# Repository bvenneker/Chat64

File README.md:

# CHAT64_C64
Chat64 for Commodore64, Sinclair ZX Spectrum, Atari 800XL, MSX and Amstrad CPC.

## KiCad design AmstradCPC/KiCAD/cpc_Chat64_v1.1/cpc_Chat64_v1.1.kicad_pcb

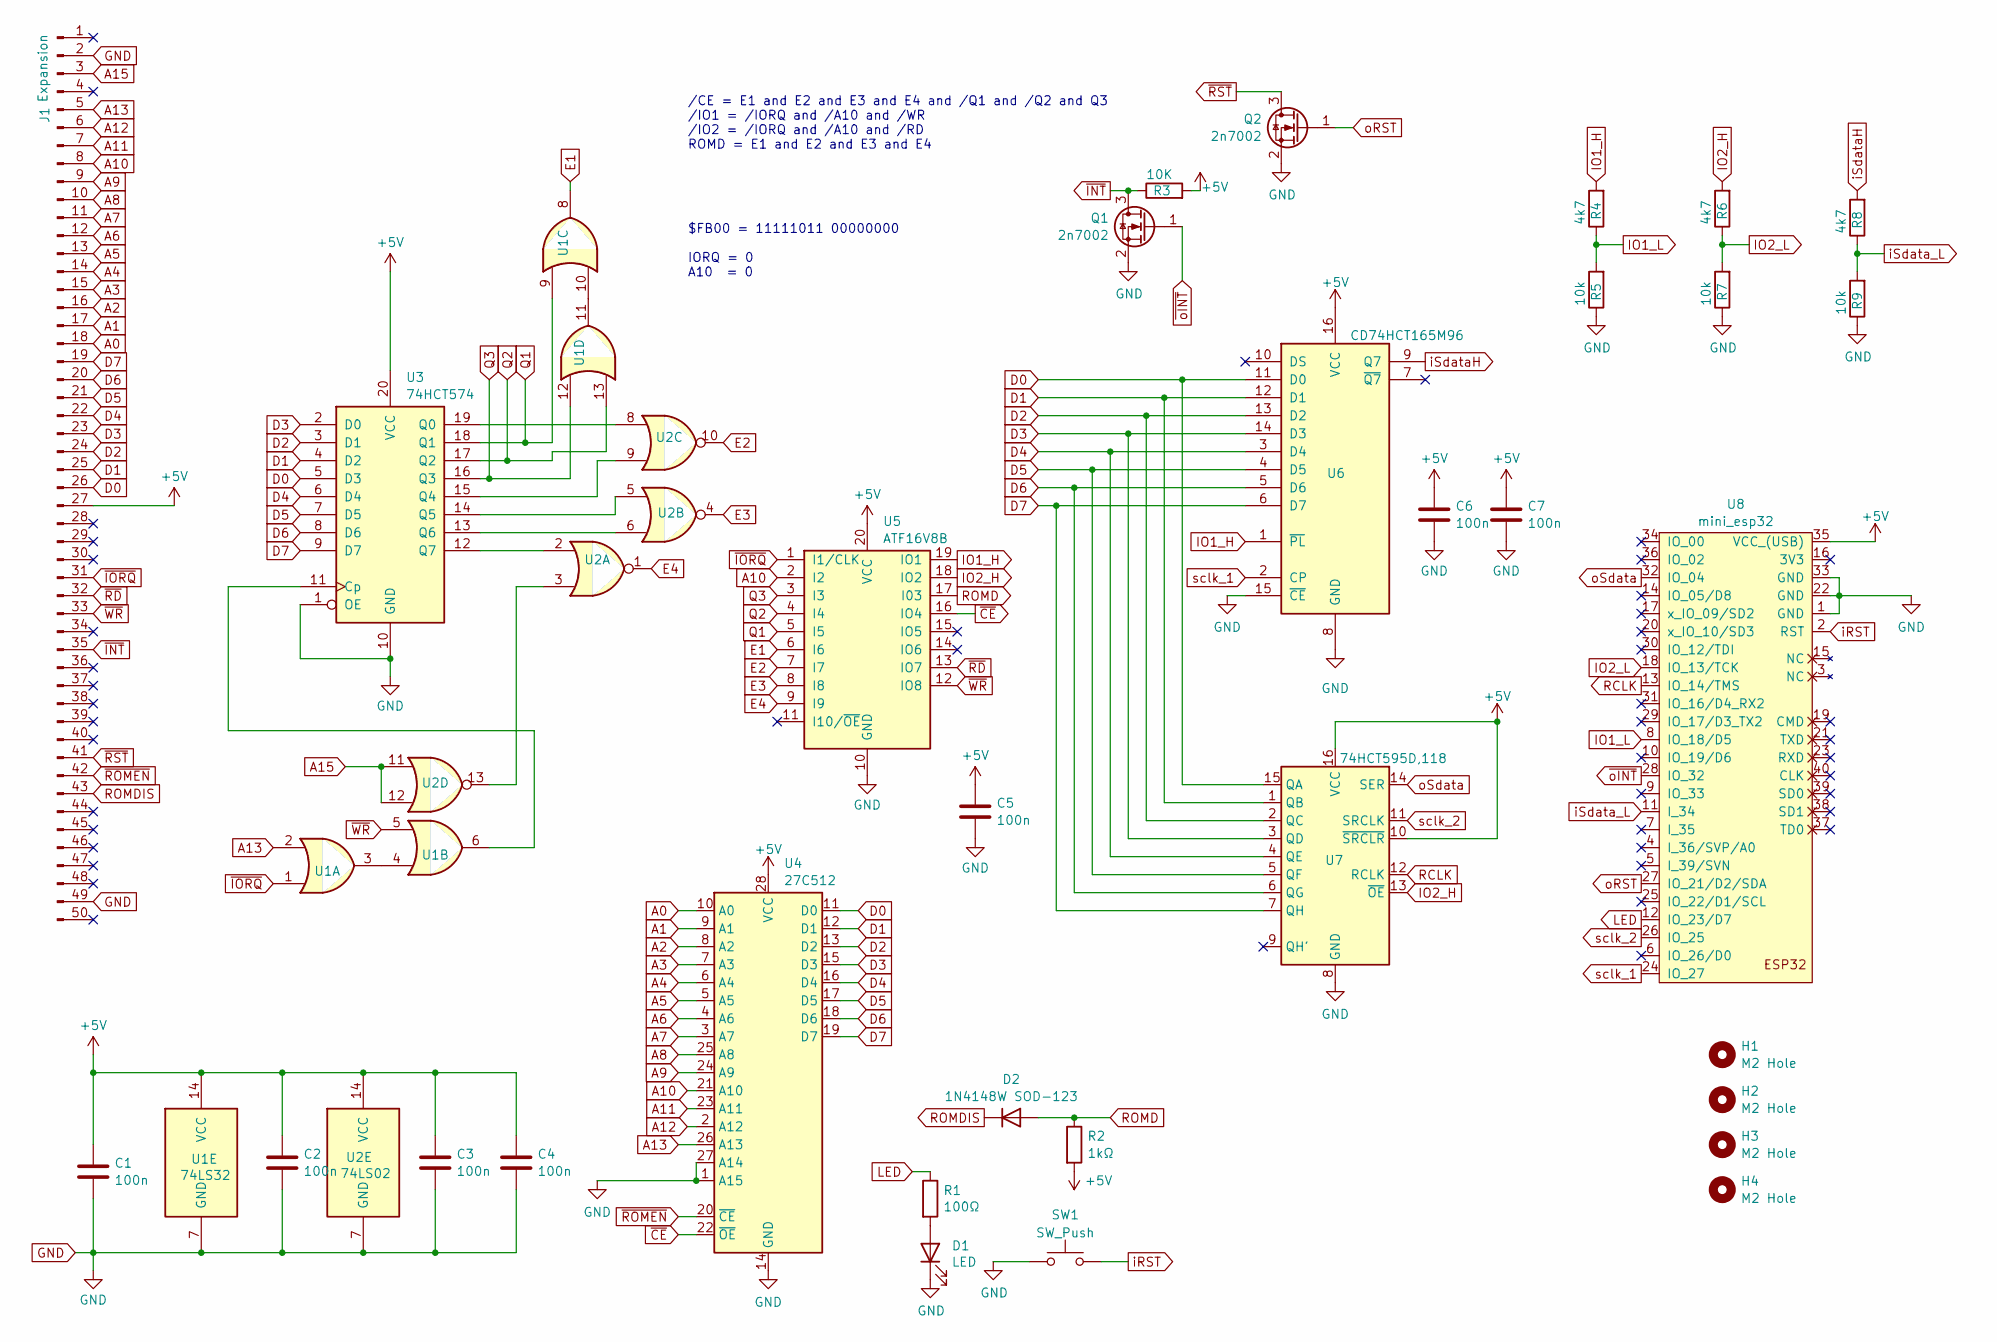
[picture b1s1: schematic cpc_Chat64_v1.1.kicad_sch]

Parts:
C1, C2, C3, C4, C5, C6, C7: 100n; C_0402_1005Metric
D1: LED; LED_0603_1608Metric
D2: 1N4148W SOD-123; D_SOD-123
H1, H2, H3, H4: M2 Hole; MountingHole_2.2mm_M2
J1: Expansion; cpc464_Expansion
Q1, Q2: 2n7002; SOT-23
R1: 100Ω; R_0402_1005Metric
R2: 1kΩ; R_0402_1005Metric
R3: 10K; R_0402_1005Metric
R4, R6, R8: 4k7; R_0402_1005Metric
R5, R7, R9: 10k; R_0402_1005Metric
SW1: SW_Push; SW_PUSH_HALF_6mm
U1: 74LS32; SO-14_3.9x8.65mm_P1.27mm
U2: 74LS02; SO-14_3.9x8.65mm_P1.27mm
U3: 74HCT574; SO-20_5.3x12.6mm_P1.27mm
U4: 27C512; DIP-28_W15.24mm_Socket_LongPads
U5: ATF16V8B; DIP-20_W7.62mm_LongPads
U6: CD74HCT165M96; SOIC-16_3.9x9.9mm_P1.27mm
U7: 74HCT595D,118; SOIC-16_3.9x9.9mm_P1.27mm
U8: mini_esp32; ESP32_mini

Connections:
+5V: C1.1, C2.1, C3.1, C4.1, C5.1, C6.1, C7.1, J1.27, R2.2, R3.2, U1.14 (VCC), U2.14 (VCC), U3.20 (VCC), U4.28 (VCC), U5.20 (VCC), U6.16 (VCC), U7.10 (~SRCLR), U7.16 (VCC), U8.35 (VCC_(USB))
A0: J1.18, U4.10 (A0)
A1: J1.17, U4.9 (A1)
A2: J1.16, U4.8 (A2)
A3: J1.15, U4.7 (A3)
A4: J1.14, U4.6 (A4)
A5: J1.13, U4.5 (A5)
A6: J1.12, U4.4 (A6)
A7: J1.11, U4.3 (A7)
A8: J1.10, U4.25 (A8)
A9: J1.9, U4.24 (A9)
A10: J1.8, U4.21 (A10), U5.2 (I2)
A11: J1.7, U4.23 (A11)
A12: J1.6, U4.2 (A12)
A13: J1.5, U1.2, U4.26 (A13)
A15: J1.3, U2.11, U2.12
D0: J1.26, U3.5 (D3), U4.11 (D0), U6.11 (D0), U7.15 (QA)
D1: J1.25, U3.4 (D2), U4.12 (D1), U6.12 (D1), U7.1 (QB)
D2: J1.24, U3.3 (D1), U4.13 (D2), U6.13 (D2), U7.2 (QC)
D3: J1.23, U3.2 (D0), U4.15 (D3), U6.14 (D3), U7.3 (QD)
D4: J1.22, U3.6 (D4), U4.16 (D4), U6.3 (D4), U7.4 (QE)
D5: J1.21, U3.7 (D5), U4.17 (D5), U6.4 (D5), U7.5 (QF)
D6: J1.20, U3.8 (D6), U4.18 (D6), U6.5 (D6), U7.6 (QG)
D7: J1.19, U3.9 (D7), U4.19 (D7), U6.6 (D7), U7.7 (QH)
E1: U1.8, U5.6 (I6)
E2: U2.10, U5.7 (I7)
E3: U2.4, U5.8 (I8)
E4: U2.1, U5.9 (I9)
GND: C1.2, C2.2, C3.2, C4.2, C5.2, C6.2, C7.2, D1.1 (K), J1.2, J1.49, Q1.2 (S), Q2.2 (S), R5.1, R7.1, R9.1, SW1.1, U1.7 (GND), U2.7 (GND), U3.1 (OE), U3.10 (GND), U4.1 (A15), U4.14 (GND), U4.27 (A14), U5.10 (GND), U6.8 (GND), U6.15 (~CE), U7.8 (GND), U8.1 (GND), U8.22 (GND), U8.33 (GND)
IO1_H: R4.2, U5.19 (IO1), U6.1 (~PL)
IO1_L: R4.1, R5.2, U8.8 (IO_18/D5)
IO2_H: R6.2, U5.18 (IO2), U7.13 (~OE)
IO2_L: R6.1, R7.2, U8.18 (IO_13/TCK)
LED: R1.1, U8.12 (IO_23/D7)
unnamed: D1.2 (A), R1.2
unnamed: U1.3, U1.4
unnamed: U1.10, U1.11
unnamed: U2.3, U2.13
unnamed: U1.6, U3.11 (Cp)
unnamed: U2.8, U3.19 (Q0)
unnamed: U2.9, U3.15 (Q4)
unnamed: U2.5, U3.14 (Q5)
unnamed: U2.6, U3.13 (Q6)
unnamed: U2.2, U3.12 (Q7)
Q1: U1.9, U3.18 (Q1), U5.5 (I5)
Q2: U1.13, U3.17 (Q2), U5.4 (I4)
Q3: U1.12, U3.16 (Q3), U5.3 (I3)
RCLK: U7.12 (RCLK), U8.13 (IO_14/TMS)
ROMD: D2.2 (A), R2.1, U5.17 (I03)
ROMDIS: D2.1 (K), J1.43
iRST: SW1.2, U8.2 (RST)
iSdataH: R8.2, U6.9 (Q7)
iSdata_L: R8.1, R9.2, U8.11 (I_34)
oRST: Q2.1 (G), U8.27 (IO_21/D2/SDA)
oSdata: U7.14 (SER), U8.32 (IO_04)
sclk_1: U6.2 (CP), U8.24 (IO_27)
sclk_2: U7.11 (SRCLK), U8.26 (IO_25)
~CE: U4.22 (~OE), U5.16 (IO4)
~INT: J1.35, Q1.3 (D), R3.1
~IORQ: J1.31, U1.1, U5.1 (I1/CLK)
~RD: J1.32, U5.13 (IO7)
~ROMEN: J1.42, U4.20 (~CE)
~RST: J1.41, Q2.3 (D)
~WR: J1.33, U1.5, U5.12 (IO8)
~oINT: Q1.1 (G), U8.28 (IO_32)

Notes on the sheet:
/CE = E1 and E2 and E3 and E4 and /Q1 and /Q2 and Q3 /IO1 = /IORQ and /A10 and /WR /IO2 = /IORQ and /A10 and /RD ROMD = E1 and E2 and E3 and E4
$FB00 = 11111011 00000000 IORQ = 0 A10 = 0

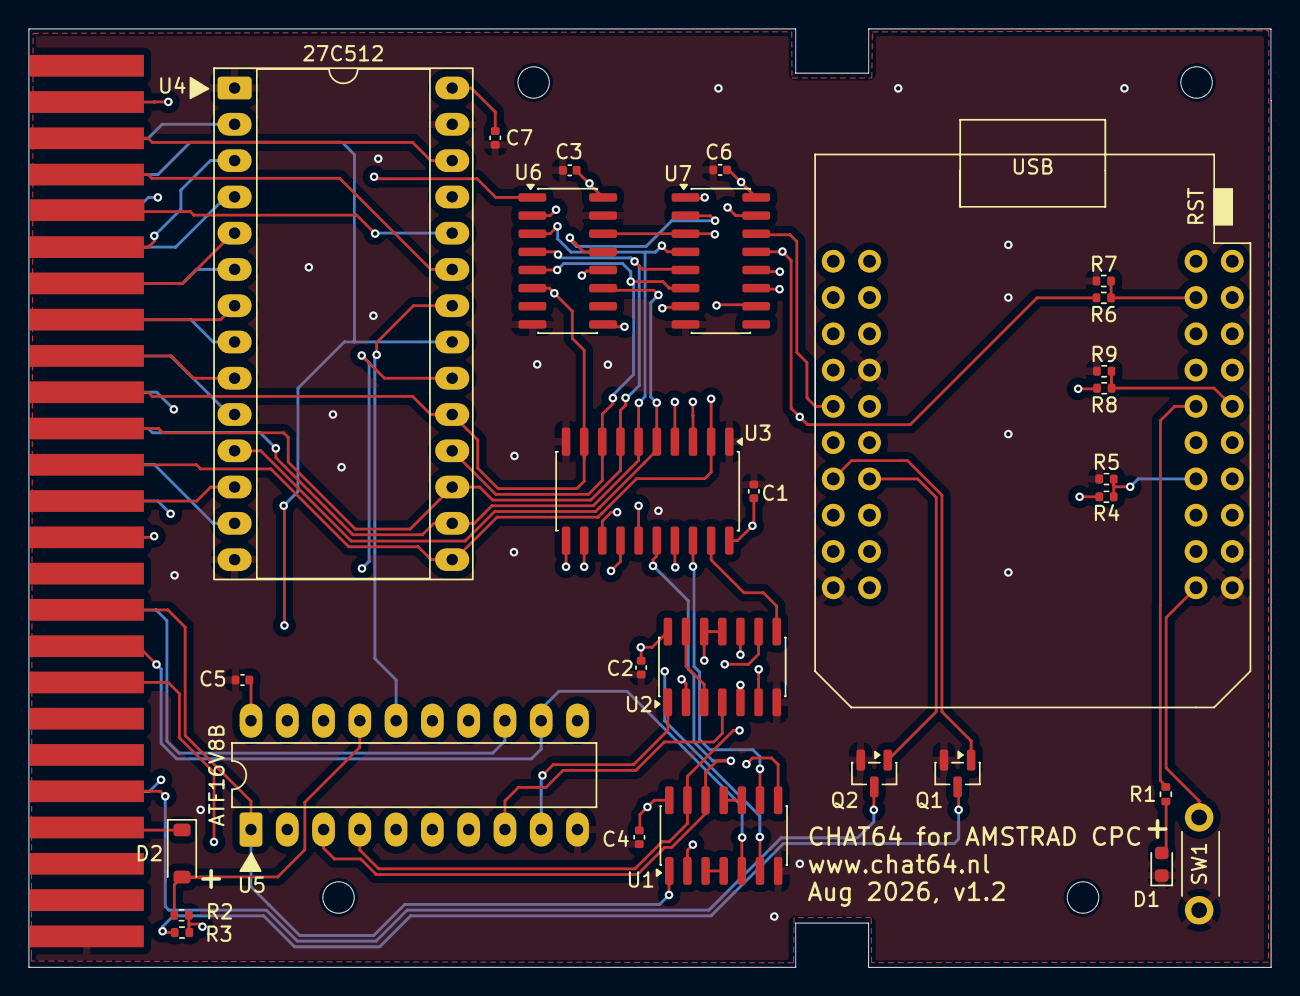
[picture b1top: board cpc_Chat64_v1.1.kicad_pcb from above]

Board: 4 copper layers, 87.0 x 65.7 mm, 34 parts (0 on the bottom side), 65 nets.

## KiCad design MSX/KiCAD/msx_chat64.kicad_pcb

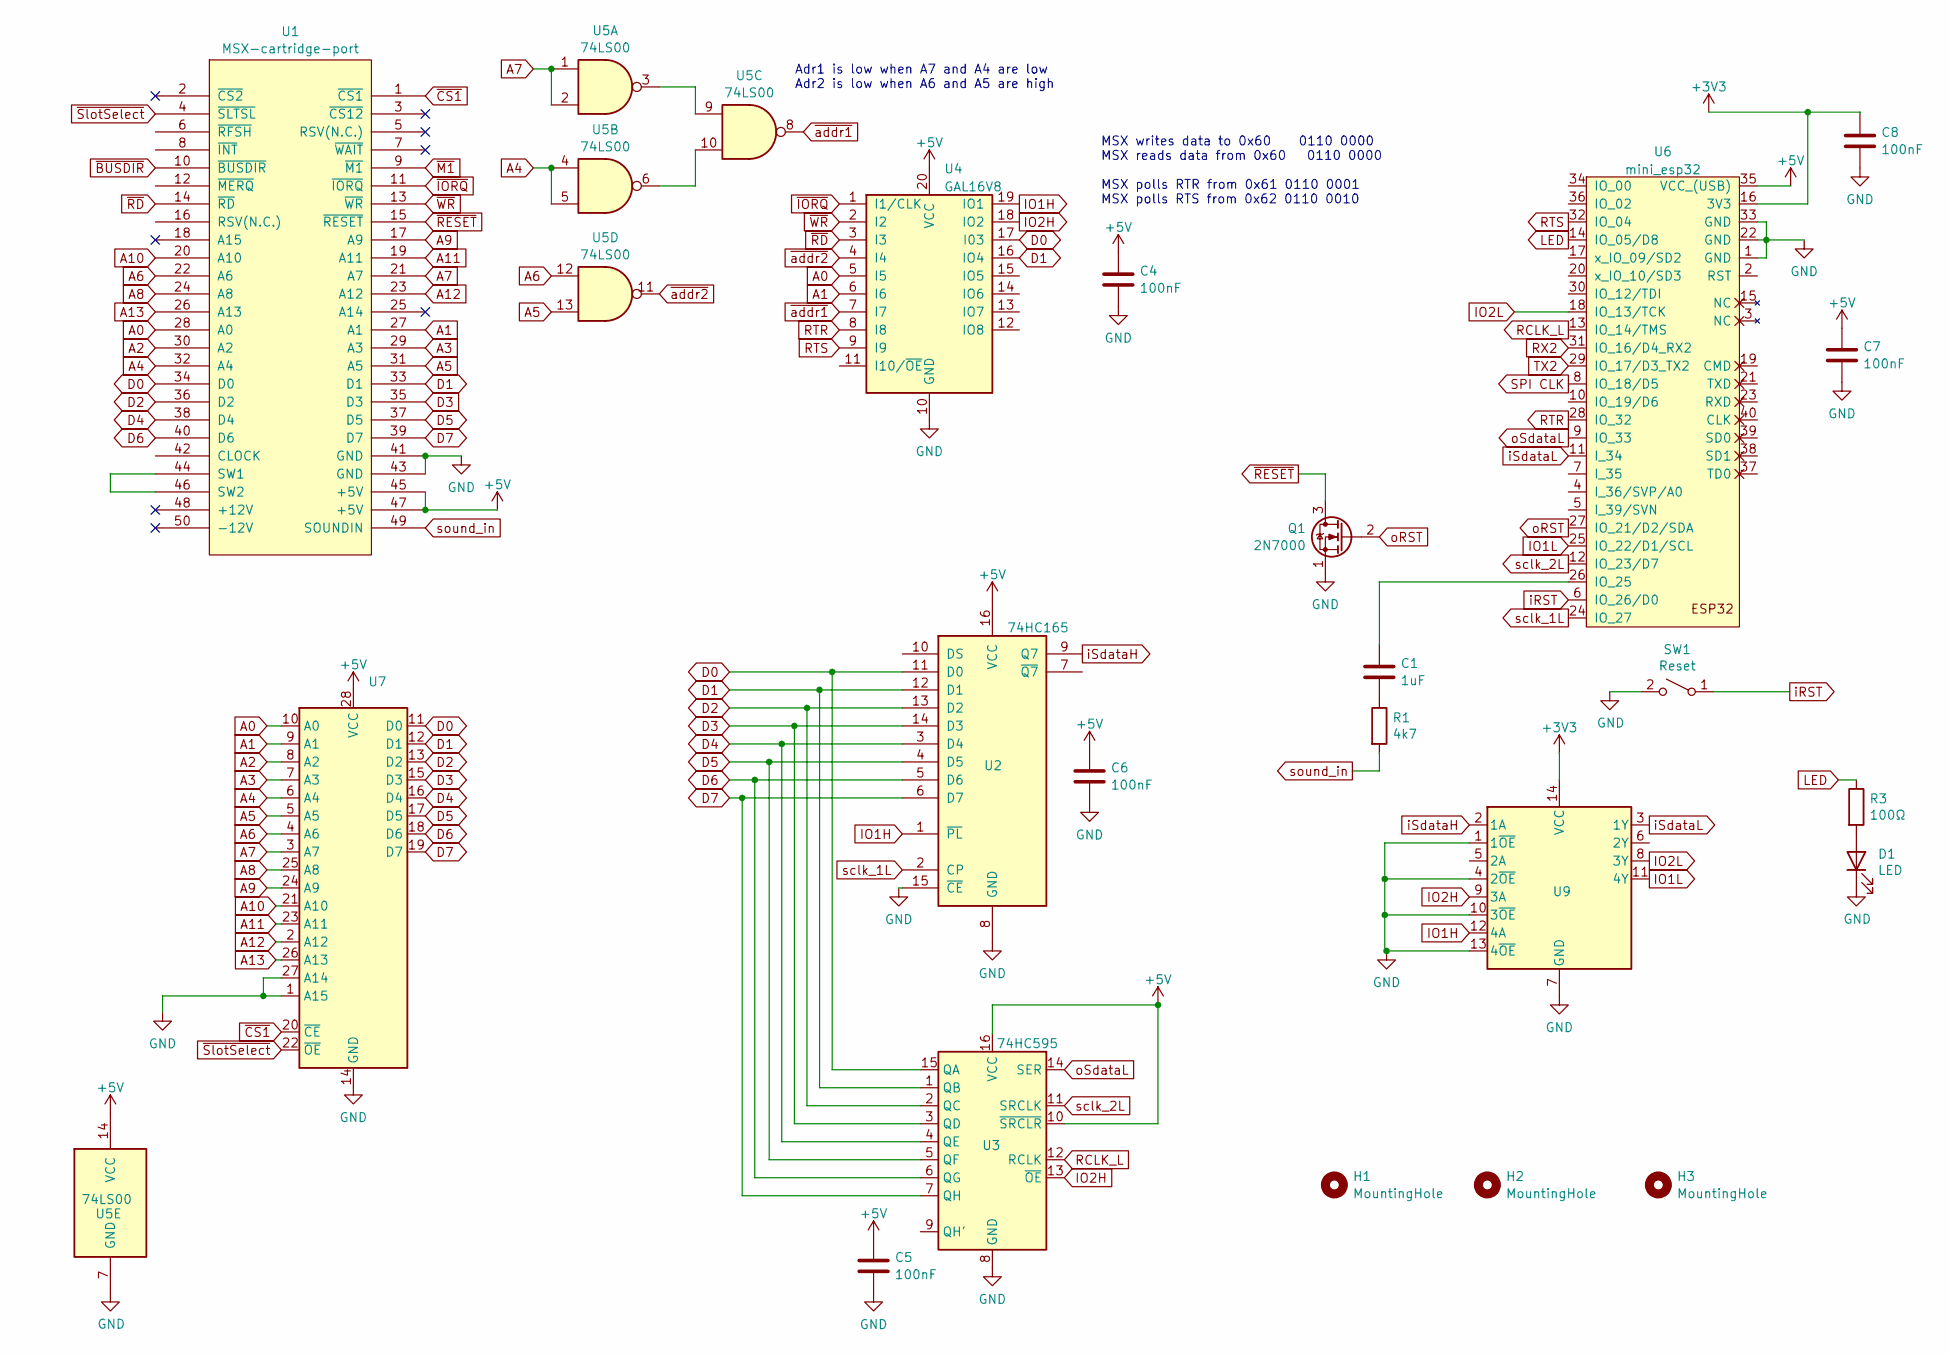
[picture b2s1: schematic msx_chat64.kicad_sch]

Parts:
C1: 1uF; C_Disc_D6.0mm_W2.5mm_P5.00mm
C4, C5, C6, C7, C8: 100nF; C_Disc_D6.0mm_W2.5mm_P5.00mm
D1: LED; LED_D3.0mm
H1, H2, H3: MountingHole; MountingHole_2.2mm_M2
Q1: 2N7000; TO-92_Inline
R1: 4k7; R_Axial_DIN0204_L3.6mm_D1.6mm_P5.08mm_Horizontal
R3: 100Ω; R_Axial_DIN0204_L3.6mm_D1.6mm_P5.08mm_Horizontal
SW1: Reset; SW_PUSH_HALF_6mm
U1: MSX-cartridge-port; MSX-Cart-NoSilkS
U2: 74HC165; DIP-16_W7.62mm_Socket_LongPads
U3: 74HC595; DIP-16_W7.62mm_Socket_LongPads
U4: GAL16V8; DIP-20_W7.62mm_Socket_LongPads
U5: 74LS00; DIP-14_W7.62mm_Socket_LongPads
U6: mini_esp32; ESP32_mini
U7: 27C512; DIP-28_W15.24mm_Socket_LongPads
U9: 74HCT125; DIP-14_W7.62mm_Socket_LongPads

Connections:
+3V3: C8.1, U6.16 (3V3), U9.14 (VCC)
+5V: C4.1, C5.1, C6.1, C7.1, U1.45 (+5V), U1.47 (+5V), U2.16 (VCC), U3.10 (~SRCLR), U3.16 (VCC), U4.20 (VCC), U5.14 (VCC), U6.35 (VCC_(USB)), U7.28 (VCC)
A0: U1.28 (A0), U4.5 (I5), U7.10 (A0)
A1: U1.27 (A1), U4.6 (I6), U7.9 (A1)
A2: U1.30 (A2), U7.8 (A2)
A3: U1.29 (A3), U7.7 (A3)
A4: U1.32 (A4), U5.4, U5.5, U7.6 (A4)
A5: U1.31 (A5), U5.13, U7.5 (A5)
A6: U1.22 (A6), U5.12, U7.4 (A6)
A7: U1.21 (A7), U5.1, U5.2, U7.3 (A7)
A8: U1.24 (A8), U7.25 (A8)
A9: U1.17 (A9), U7.24 (A9)
A10: U1.20 (A10), U7.21 (A10)
A11: U1.19 (A11), U7.23 (A11)
A12: U1.23 (A12), U7.2 (A12)
A13: U1.26 (A13), U7.26 (A13)
D0: U1.34 (D0), U2.11 (D0), U3.15 (QA), U4.17 (I03), U7.11 (D0)
D1: U1.33 (D1), U2.12 (D1), U3.1 (QB), U4.16 (IO4), U7.12 (D1)
D2: U1.36 (D2), U2.13 (D2), U3.2 (QC), U7.13 (D2)
D3: U1.35 (D3), U2.14 (D3), U3.3 (QD), U7.15 (D3)
D4: U1.38 (D4), U2.3 (D4), U3.4 (QE), U7.16 (D4)
D5: U1.37 (D5), U2.4 (D5), U3.5 (QF), U7.17 (D5)
D6: U1.40 (D6), U2.5 (D6), U3.6 (QG), U7.18 (D6)
D7: U1.39 (D7), U2.6 (D7), U3.7 (QH), U7.19 (D7)
GND: C4.2, C5.2, C6.2, C7.2, C8.2, D1.1 (K), Q1.1 (S), SW1.2 (B), U1.41 (GND), U1.43 (GND), U2.8 (GND), U2.15 (~CE), U3.8 (GND), U4.10 (GND), U5.7 (GND), U6.1 (GND), U6.22 (GND), U6.33 (GND), U7.1 (A15), U7.14 (GND), U7.27 (A14), U9.1 (1~OE), U9.4 (2~OE), U9.7 (GND), U9.10 (3~OE), U9.13 (4~OE)
IO1H: U2.1 (~PL), U4.19 (IO1), U9.12 (4A)
IO1L: U6.25 (IO_22/D1/SCL), U9.11 (4Y)
IO2H: U3.13 (~OE), U4.18 (IO2), U9.9 (3A)
IO2L: U6.18 (IO_13/TCK), U9.8 (3Y)
LED: R3.1, U6.14 (IO_05/D8)
unnamed: C1.2, R1.1
unnamed: D1.2 (A), R3.2
unnamed: U1.44 (SW1), U1.46 (SW2)
unnamed: U5.3, U5.9
unnamed: U5.6, U5.10
unnamed: C1.1, U6.26 (IO_25)
RCLK_L: U3.12 (RCLK), U6.13 (IO_14/TMS)
RTR: U4.8 (I8), U6.28 (IO_32)
RTS: U4.9 (I9), U6.32 (IO_04)
RX2: U6.31 (IO_16/D4_RX2)
SPI CLK: U6.8 (IO_18/D5)
TX2: U6.29 (IO_17/D3_TX2)
iRST: SW1.1 (A), U6.6 (IO_26/D0)
iSdataH: U2.9 (Q7), U9.2 (1A)
iSdataL: U6.11 (I_34), U9.3 (1Y)
oRST: Q1.2 (G), U6.27 (IO_21/D2/SDA)
oSdataL: U3.14 (SER), U6.9 (IO_33)
sclk_1L: U2.2 (CP), U6.24 (IO_27)
sclk_2L: U3.11 (SRCLK), U6.12 (IO_23/D7)
sound_in: R1.2, U1.49 (SOUNDIN)
~BUSDIR: U1.10 (~BUSDIR)
~CS1: U1.1 (~CS1), U7.20 (~CE)
~IORQ: U1.11 (~IORQ), U4.1 (I1/CLK)
~M1: U1.9 (~M1)
~RD: U1.14 (~RD), U4.3 (I3)
~RESET: Q1.3 (D), U1.15 (~RESET)
~SlotSelect: U1.4 (~SLTSL), U7.22 (~OE)
~WR: U1.13 (~WR), U4.2 (I2)
~addr1: U4.7 (I7), U5.8
~addr2: U4.4 (I4), U5.11

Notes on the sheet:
Adr1 is low when A7 and A4 are low Adr2 is low when A6 and A5 are high
MSX writes data to 0x60 0110 0000 MSX reads data from 0x60 0110 0000 MSX polls RTR from 0x61 0110 0001 MSX polls RTS from 0x62 0110 0010

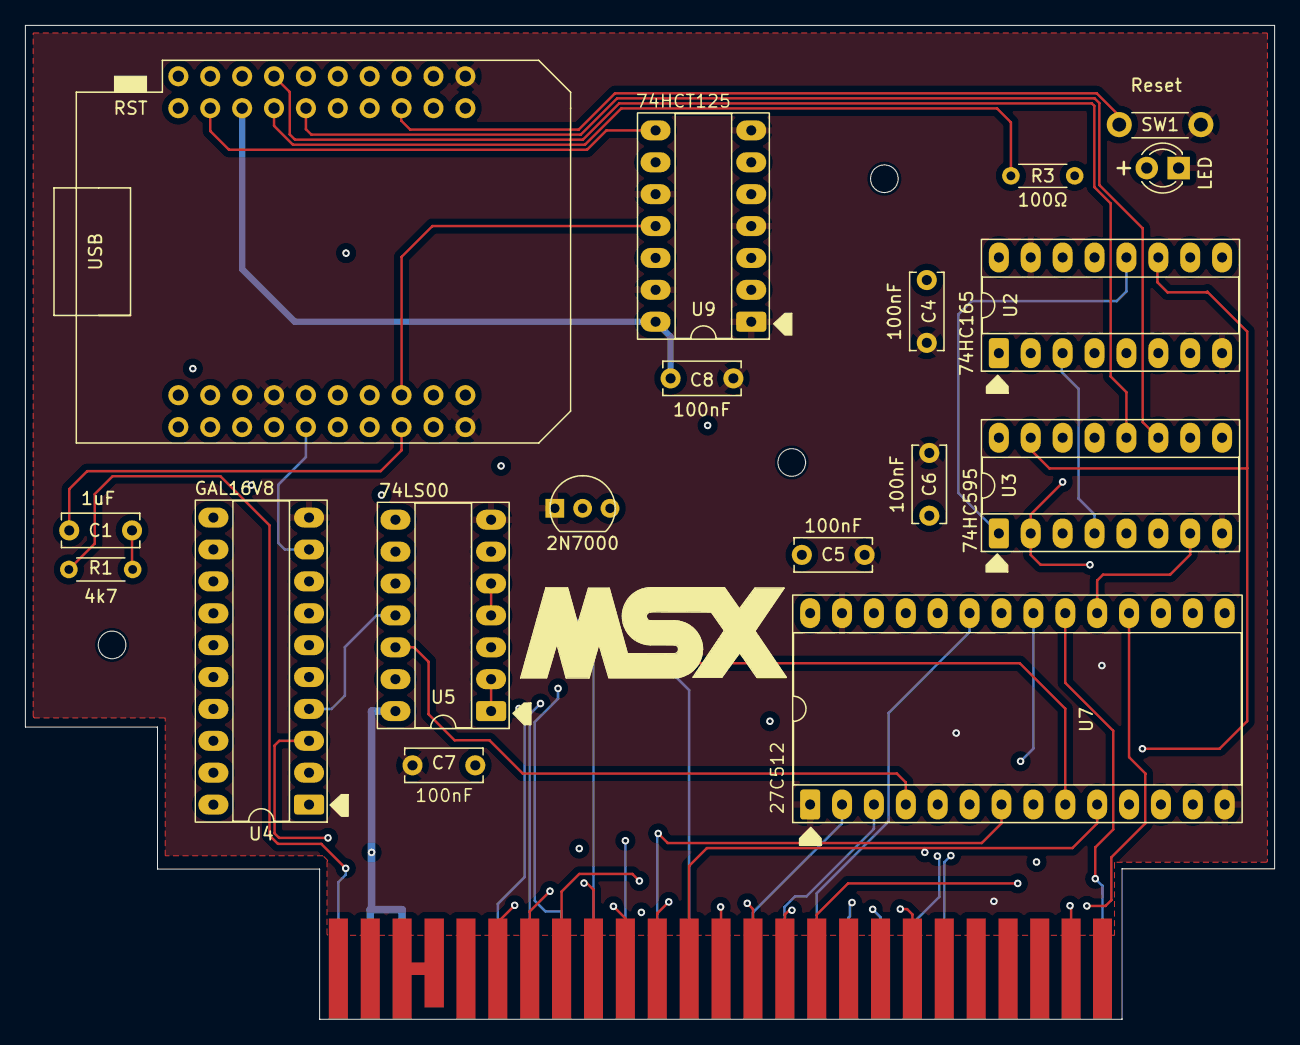
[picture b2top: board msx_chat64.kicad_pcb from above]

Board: 4 copper layers, 99.5 x 79.2 mm, 22 parts (0 on the bottom side), 55 nets.

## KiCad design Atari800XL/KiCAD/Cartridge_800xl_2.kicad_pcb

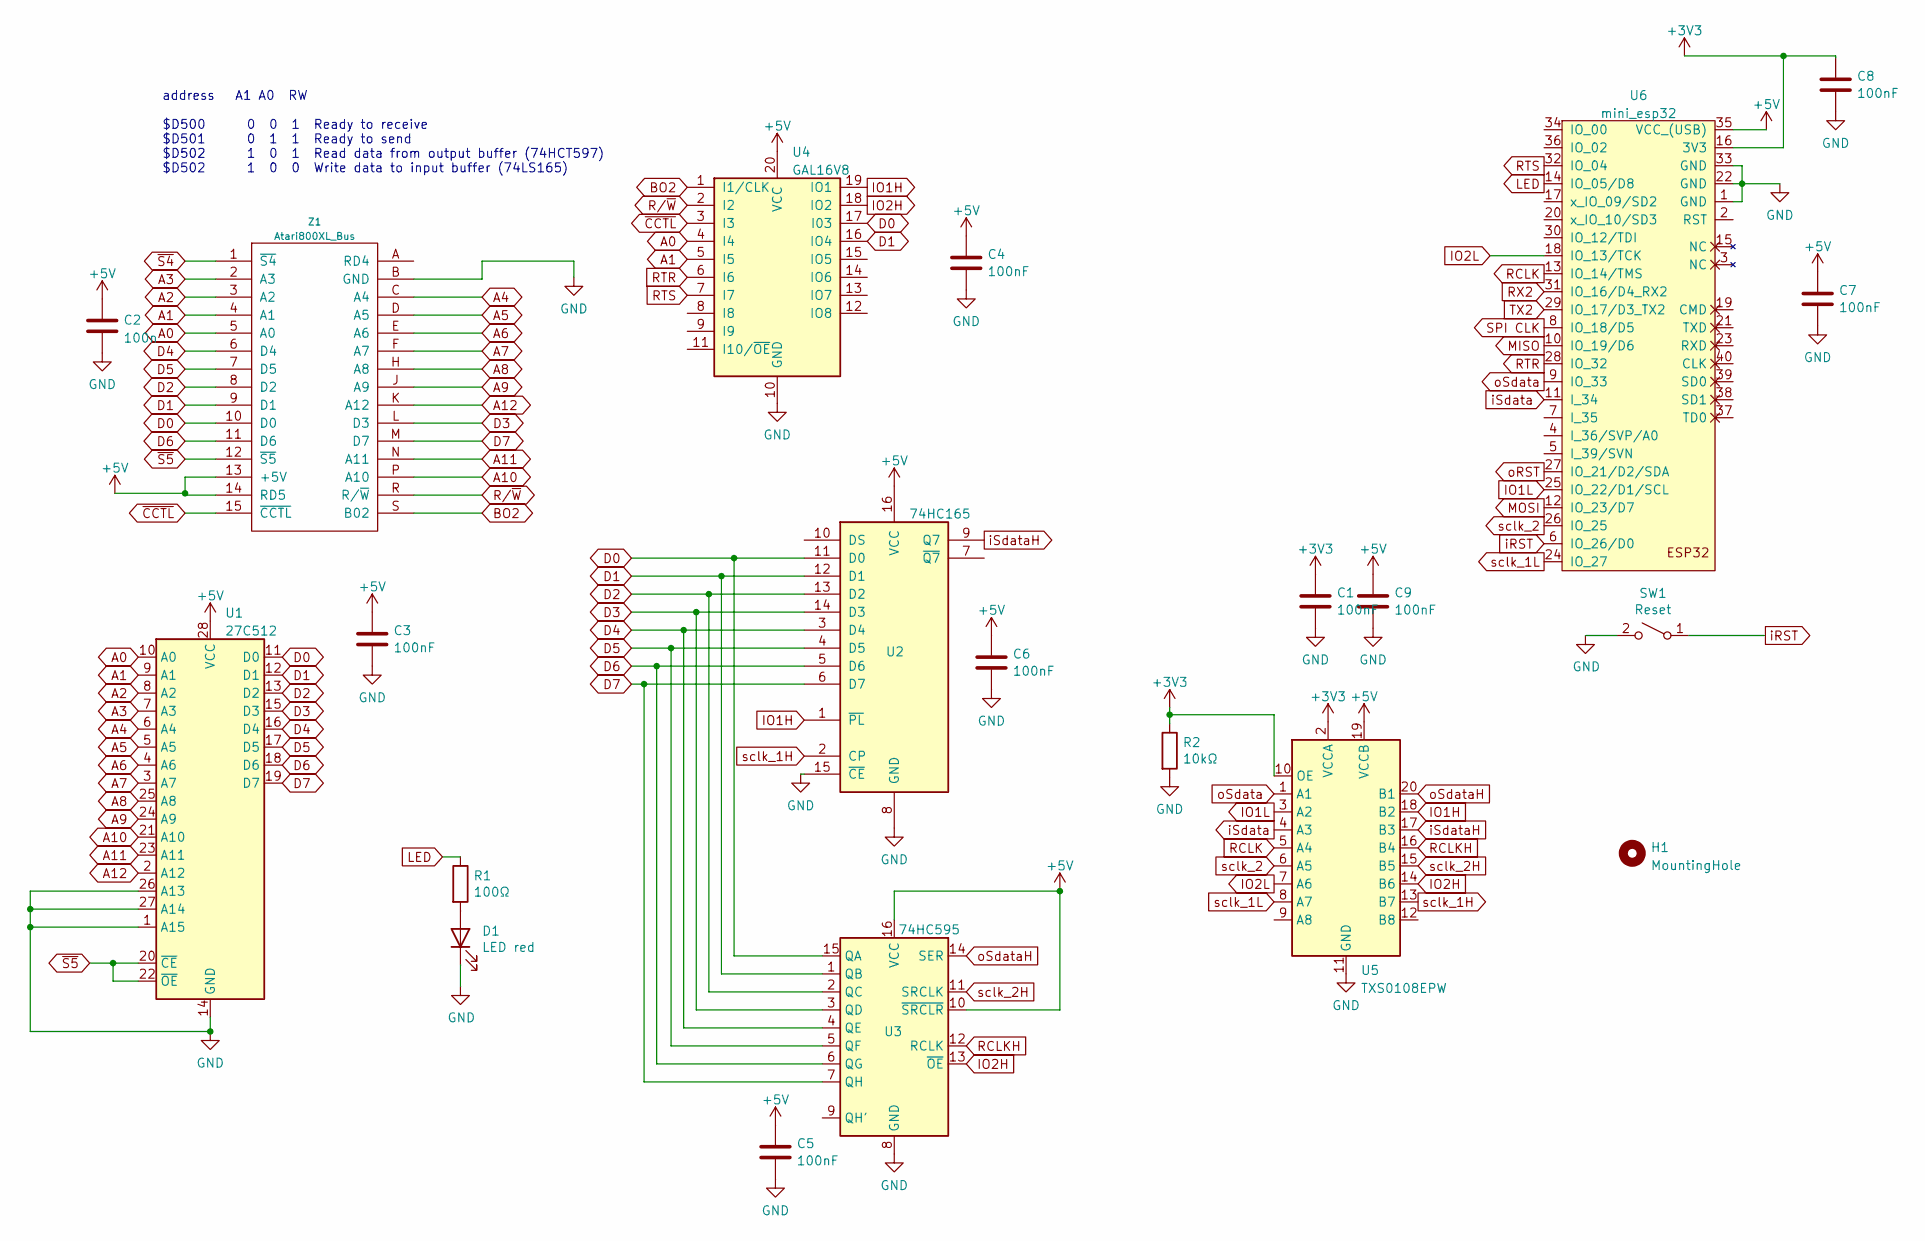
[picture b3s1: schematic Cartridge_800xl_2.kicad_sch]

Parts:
C1, C3, C4, C5, C6, C7, C8, C9: 100nF; C_0402_1005Metric
C2: 100n; C_0402_1005Metric
D1: LED red; LED_0603_1608Metric
H1: MountingHole; MountingHole_3.2mm_M3
R1: 100Ω; R_0402_1005Metric
R2: 10kΩ; R_0402_1005Metric
SW1: Reset; SW_PUSH_HALF_6mm
U1: 27C512; DIP-28_W15.24mm_LongPads
U2: 74HC165; SOIC-16_3.9x9.9mm_P1.27mm
U3: 74HC595; SOIC-16_3.9x9.9mm_P1.27mm
U4: GAL16V8; DIP-20_W7.62mm_LongPads
U5: TXS0108EPW; TSSOP-20_4.4x6.5mm_P0.65mm
U6: mini_esp32; ESP32_mini
Z1: Atari800XL_Bus; Atari_bus

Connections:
+3V3: C1.1, C8.1, R2.1, U5.2 (VCCA), U5.10 (OE), U6.16 (3V3)
+5V: C2.1, C3.1, C4.1, C5.1, C6.1, C7.1, C9.1, U1.28 (VCC), U2.16 (VCC), U3.10 (~SRCLR), U3.16 (VCC), U4.20 (VCC), U5.19 (VCCB), U6.35 (VCC_(USB)), Z1.13 (+5V), Z1.14 (RD5)
A0: U1.10 (A0), U4.4 (I4), Z1.5 (A0)
A1: U1.9 (A1), U4.5 (I5), Z1.4 (A1)
A2: U1.8 (A2), Z1.3 (A2)
A3: U1.7 (A3), Z1.2 (A3)
A4: U1.6 (A4), Z1.C (A4)
A5: U1.5 (A5), Z1.D (A5)
A6: U1.4 (A6), Z1.E (A6)
A7: U1.3 (A7), Z1.F (A7)
A8: U1.25 (A8), Z1.H (A8)
A9: U1.24 (A9), Z1.J (A9)
A10: U1.21 (A10), Z1.P (A10)
A11: U1.23 (A11), Z1.N (A11)
A12: U1.2 (A12), Z1.K (A12)
BO2: U4.1 (I1/CLK), Z1.S (B02)
D0: U1.11 (D0), U2.11 (D0), U3.15 (QA), U4.17 (I03), Z1.10 (D0)
D1: U1.12 (D1), U2.12 (D1), U3.1 (QB), U4.16 (IO4), Z1.9 (D1)
D2: U1.13 (D2), U2.13 (D2), U3.2 (QC), Z1.8 (D2)
D3: U1.15 (D3), U2.14 (D3), U3.3 (QD), Z1.L (D3)
D4: U1.16 (D4), U2.3 (D4), U3.4 (QE), Z1.6 (D4)
D5: U1.17 (D5), U2.4 (D5), U3.5 (QF), Z1.7 (D5)
D6: U1.18 (D6), U2.5 (D6), U3.6 (QG), Z1.11 (D6)
D7: U1.19 (D7), U2.6 (D7), U3.7 (QH), Z1.M (D7)
GND: C1.2, C2.2, C3.2, C4.2, C5.2, C6.2, C7.2, C8.2, C9.2, D1.1 (K), R2.2, SW1.2 (B), U1.1 (A15), U1.14 (GND), U1.26 (A13), U1.27 (A14), U2.8 (GND), U2.15 (~CE), U3.8 (GND), U4.10 (GND), U5.11 (GND), U6.1 (GND), U6.22 (GND), U6.33 (GND), Z1.B (GND)
IO1H: U2.1 (~PL), U4.19 (IO1), U5.18 (B2)
IO1L: U5.3 (A2), U6.25 (IO_22/D1/SCL)
IO2H: U3.13 (~OE), U4.18 (IO2), U5.14 (B6)
IO2L: U5.7 (A6), U6.18 (IO_13/TCK)
LED: R1.1, U6.14 (IO_05/D8)
MISO: U6.10 (IO_19/D6)
MOSI: U6.12 (IO_23/D7)
unnamed: D1.2 (A), R1.2
RCLK: U5.5 (A4), U6.13 (IO_14/TMS)
RCLKH: U3.12 (RCLK), U5.16 (B4)
RTR: U4.6 (I6), U6.28 (IO_32)
RTS: U4.7 (I7), U6.32 (IO_04)
RX2: U6.31 (IO_16/D4_RX2)
R/~W: U4.2 (I2), Z1.R (R/~W)
SPI CLK: U6.8 (IO_18/D5)
TX2: U6.29 (IO_17/D3_TX2)
iRST: SW1.1 (A), U6.6 (IO_26/D0)
iSdata: U5.4 (A3), U6.11 (I_34)
iSdataH: U2.9 (Q7), U5.17 (B3)
oRST: U6.27 (IO_21/D2/SDA)
oSdata: U5.1 (A1), U6.9 (IO_33)
oSdataH: U3.14 (SER), U5.20 (B1)
sclk_1H: U2.2 (CP), U5.13 (B7)
sclk_1L: U5.8 (A7), U6.24 (IO_27)
sclk_2: U5.6 (A5), U6.26 (IO_25)
sclk_2H: U3.11 (SRCLK), U5.15 (B5)
~CCTL: U4.3 (I3), Z1.15 (~CCTL)
~S4: Z1.1 (~S4)
~S5: U1.20 (~CE), U1.22 (~OE), Z1.12 (~S5)

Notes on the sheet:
address A1 A0 RW $D500 0 0 1 Ready to receive $D501 0 1 1 Ready to send $D502 1 0 1 Read data from output buffer (74HCT597) $D502 1 0 0 Write data to input buffer (74LS165)

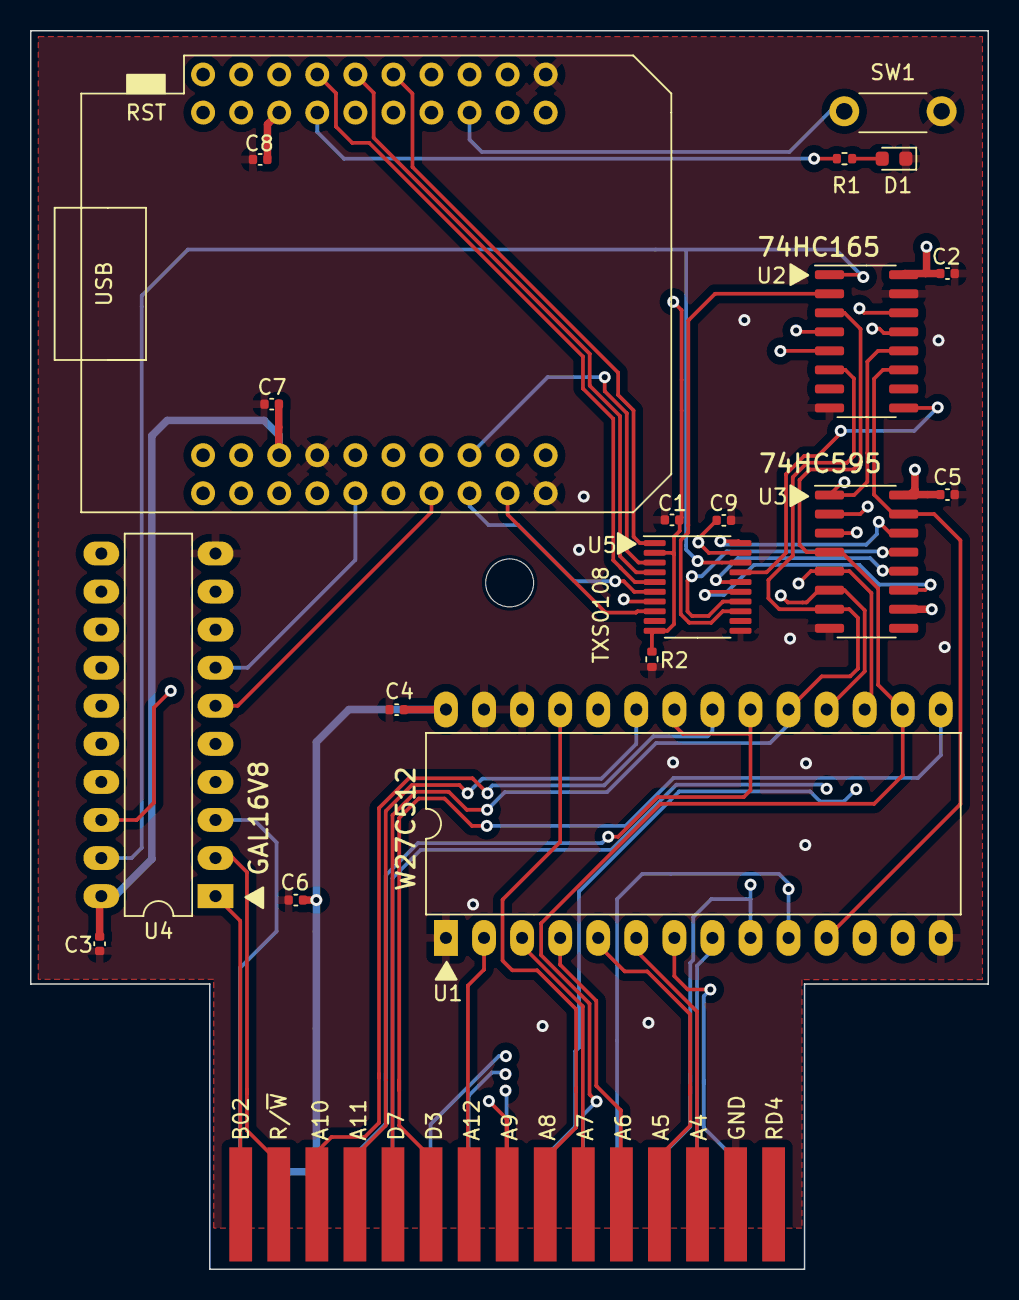
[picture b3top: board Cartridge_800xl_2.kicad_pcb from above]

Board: 4 copper layers, 63.9 x 82.6 mm, 21 parts (0 on the bottom side), 47 nets.

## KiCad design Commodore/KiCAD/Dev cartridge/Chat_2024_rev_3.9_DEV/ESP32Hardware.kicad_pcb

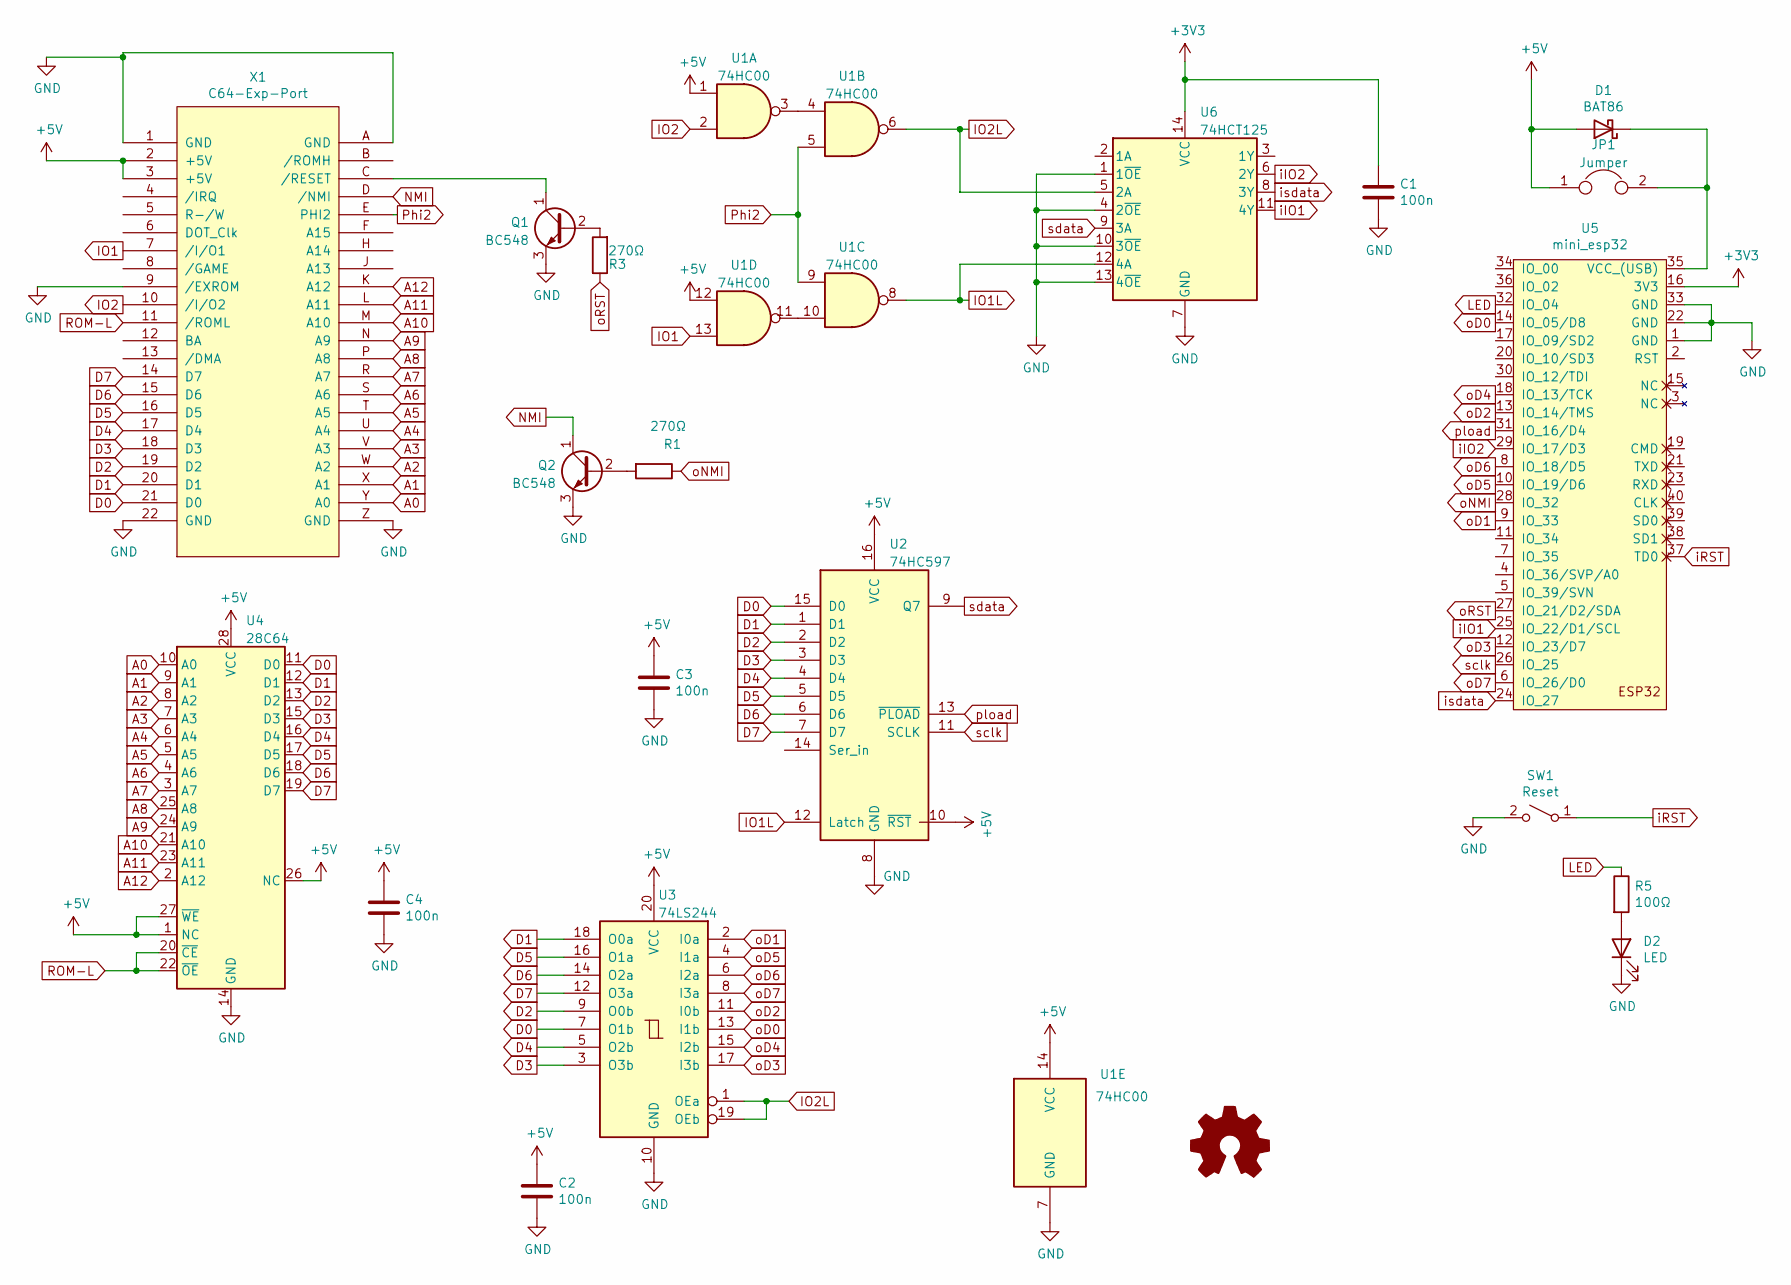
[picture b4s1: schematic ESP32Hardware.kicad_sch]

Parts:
C1, C2, C3, C4: 100n; C_Disc_D4.3mm_W1.9mm_P5.00mm
D1: BAT86; D_DO-34_SOD68_P7.62mm_Horizontal
D2: LED; LED_D3.0mm
JP1: Jumper; PinHeader_1x02_P2.54mm_Vertical
LOGO1: Logo_Open_Hardware_Small; OSHW-Logo2_14.6x12mm_SilkScreen
Q1, Q2: BC548; TO-92_Inline
R1, R3: 270Ω; R_Axial_DIN0204_L3.6mm_D1.6mm_P5.08mm_Horizontal
R5: 100Ω; R_Axial_DIN0204_L3.6mm_D1.6mm_P5.08mm_Horizontal
SW1: Reset; SW_PUSH_6mm
U1: 74HC00; DIP-14_W7.62mm_LongPads
U2: 74HC597; DIP-16_W7.62mm_LongPads
U3: 74LS244; DIP-20_W7.62mm_LongPads
U4: 28C64; 28ZIF600_2
U5: mini_esp32; ESP32_mini
U6: 74HCT125; DIP-14_W7.62mm_LongPads
X1: C64-Exp-Port; C64-Cart-NoSilkS

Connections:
+3V3: C1.1, U5.16 (3V3), U6.14 (VCC)
+5V: C2.1, C3.1, C4.1, D1.2 (A), JP1.1, U1.1, U1.12, U1.14 (VCC), U2.10 (~RST), U2.16 (VCC), U3.20 (VCC), U4.1 (NC), U4.26 (NC), U4.27 (~WE), U4.28 (VCC), X1.2 (+5V), X1.3 (+5V)
A0: U4.10 (A0), X1.Y (A0)
A1: U4.9 (A1), X1.X (A1)
A2: U4.8 (A2), X1.W (A2)
A3: U4.7 (A3), X1.V (A3)
A4: U4.6 (A4), X1.U (A4)
A5: U4.5 (A5), X1.T (A5)
A6: U4.4 (A6), X1.S (A6)
A7: U4.3 (A7), X1.R (A7)
A8: U4.25 (A8), X1.P (A8)
A9: U4.24 (A9), X1.N (A9)
A10: U4.21 (A10), X1.M (A10)
A11: U4.23 (A11), X1.L (A11)
A12: U4.2 (A12), X1.K (A12)
D0: U2.15 (D0), U3.7 (O1b), U4.11 (D0), X1.21 (D0)
D1: U2.1 (D1), U3.18 (O0a), U4.12 (D1), X1.20 (D1)
D2: U2.2 (D2), U3.9 (O0b), U4.13 (D2), X1.19 (D2)
D3: U2.3 (D3), U3.3 (O3b), U4.15 (D3), X1.18 (D3)
D4: U2.4 (D4), U3.5 (O2b), U4.16 (D4), X1.17 (D4)
D5: U2.5 (D5), U3.16 (O1a), U4.17 (D5), X1.16 (D5)
D6: U2.6 (D6), U3.14 (O2a), U4.18 (D6), X1.15 (D6)
D7: U2.7 (D7), U3.12 (O3a), U4.19 (D7), X1.14 (D7)
GND: C1.2, C2.2, C3.2, C4.2, D2.1 (K), Q1.3 (E), Q2.3 (E), SW1.2 (B), U1.7 (GND), U2.8 (GND), U3.10 (GND), U4.14 (GND), U5.1 (GND), U5.22 (GND), U5.33 (GND), U6.1 (1~OE), U6.4 (2~OE), U6.7 (GND), U6.10 (3~OE), U6.13 (4~OE), X1.1 (GND), X1.9 (/EXROM), X1.22 (GND), X1.A (GND), X1.Z (GND)
IO1: U1.13, X1.7 (/I/O1)
IO1L: U1.8, U2.12 (Latch), U6.12 (4A)
IO2: U1.2, X1.10 (/I/O2)
IO2L: U1.6, U3.1 (OEa), U3.19 (OEb), U6.5 (2A)
LED: R5.1, U5.32 (IO_04)
NMI: Q2.1 (C), X1.D (/NMI)
unnamed: D1.1 (K), JP1.2, U5.35 (VCC_(USB))
unnamed: D2.2 (A), R5.2
unnamed: Q1.1 (C), X1.C (/RESET)
unnamed: Q1.2 (B), R3.2
unnamed: Q2.2 (B), R1.2
unnamed: U1.3, U1.4
unnamed: U1.10, U1.11
Phi2: U1.5, U1.9, X1.E (PHI2)
ROM-L: U4.20 (~CE), U4.22 (~OE), X1.11 (/ROML)
iIO1: U5.25 (IO_22/D1/SCL), U6.11 (4Y)
iIO2: U5.29 (IO_17/D3), U6.6 (2Y)
iRST: SW1.1 (A), U5.37 (TD0)
isdata: U5.24 (IO_27), U6.8 (3Y)
oD0: U3.13 (I1b), U5.14 (IO_05/D8)
oD1: U3.2 (I0a), U5.9 (IO_33)
oD2: U3.11 (I0b), U5.13 (IO_14/TMS)
oD3: U3.17 (I3b), U5.12 (IO_23/D7)
oD4: U3.15 (I2b), U5.18 (IO_13/TCK)
oD5: U3.4 (I1a), U5.10 (IO_19/D6)
oD6: U3.6 (I2a), U5.8 (IO_18/D5)
oD7: U3.8 (I3a), U5.6 (IO_26/D0)
oNMI: R1.1, U5.28 (IO_32)
oRST: R3.1, U5.27 (IO_21/D2/SDA)
pload: U2.13 (~PLOAD), U5.31 (IO_16/D4)
sclk: U2.11 (SCLK), U5.26 (IO_25)
sdata: U2.9 (Q7), U6.9 (3A)

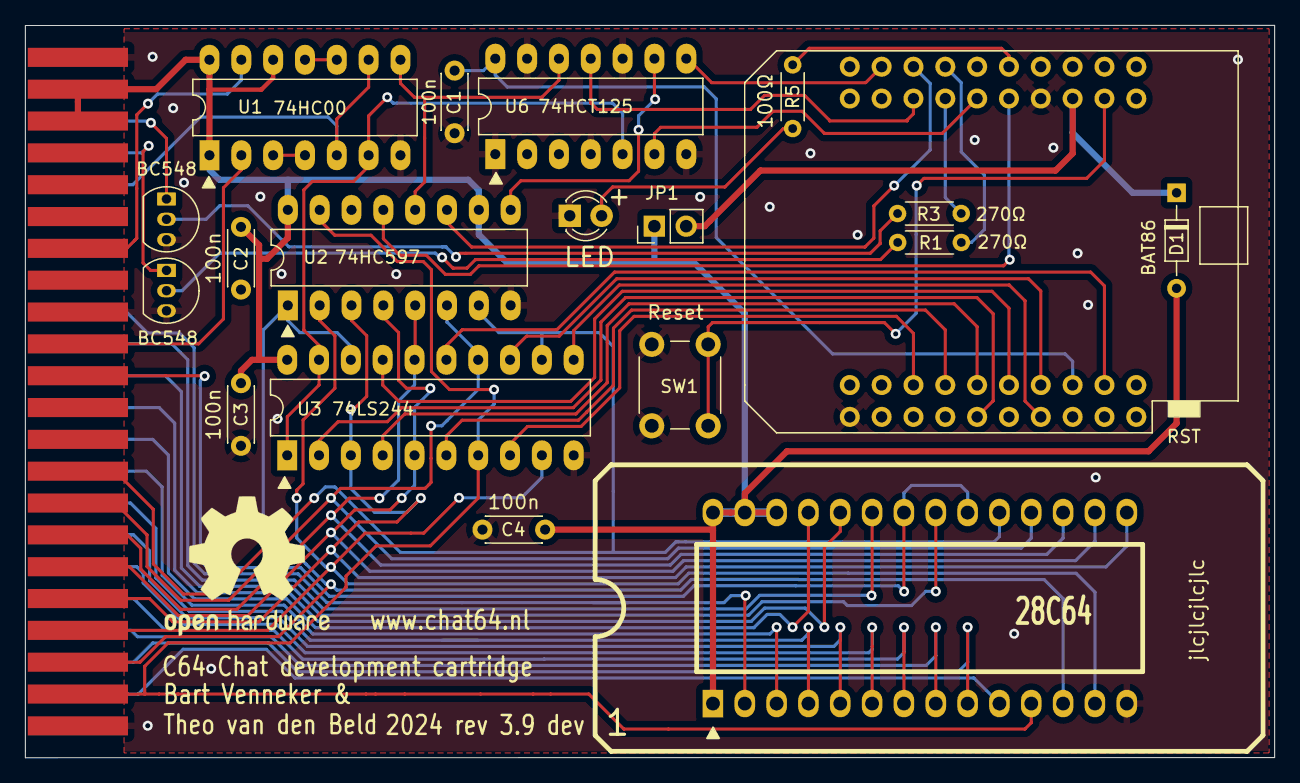
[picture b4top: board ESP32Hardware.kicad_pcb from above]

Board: 2 copper layers, 99.7 x 58.4 mm, 21 parts (0 on the bottom side), 56 nets.
